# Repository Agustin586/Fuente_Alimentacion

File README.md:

# Fuente_Alimentacion
 Programa de esp32 y kicad.

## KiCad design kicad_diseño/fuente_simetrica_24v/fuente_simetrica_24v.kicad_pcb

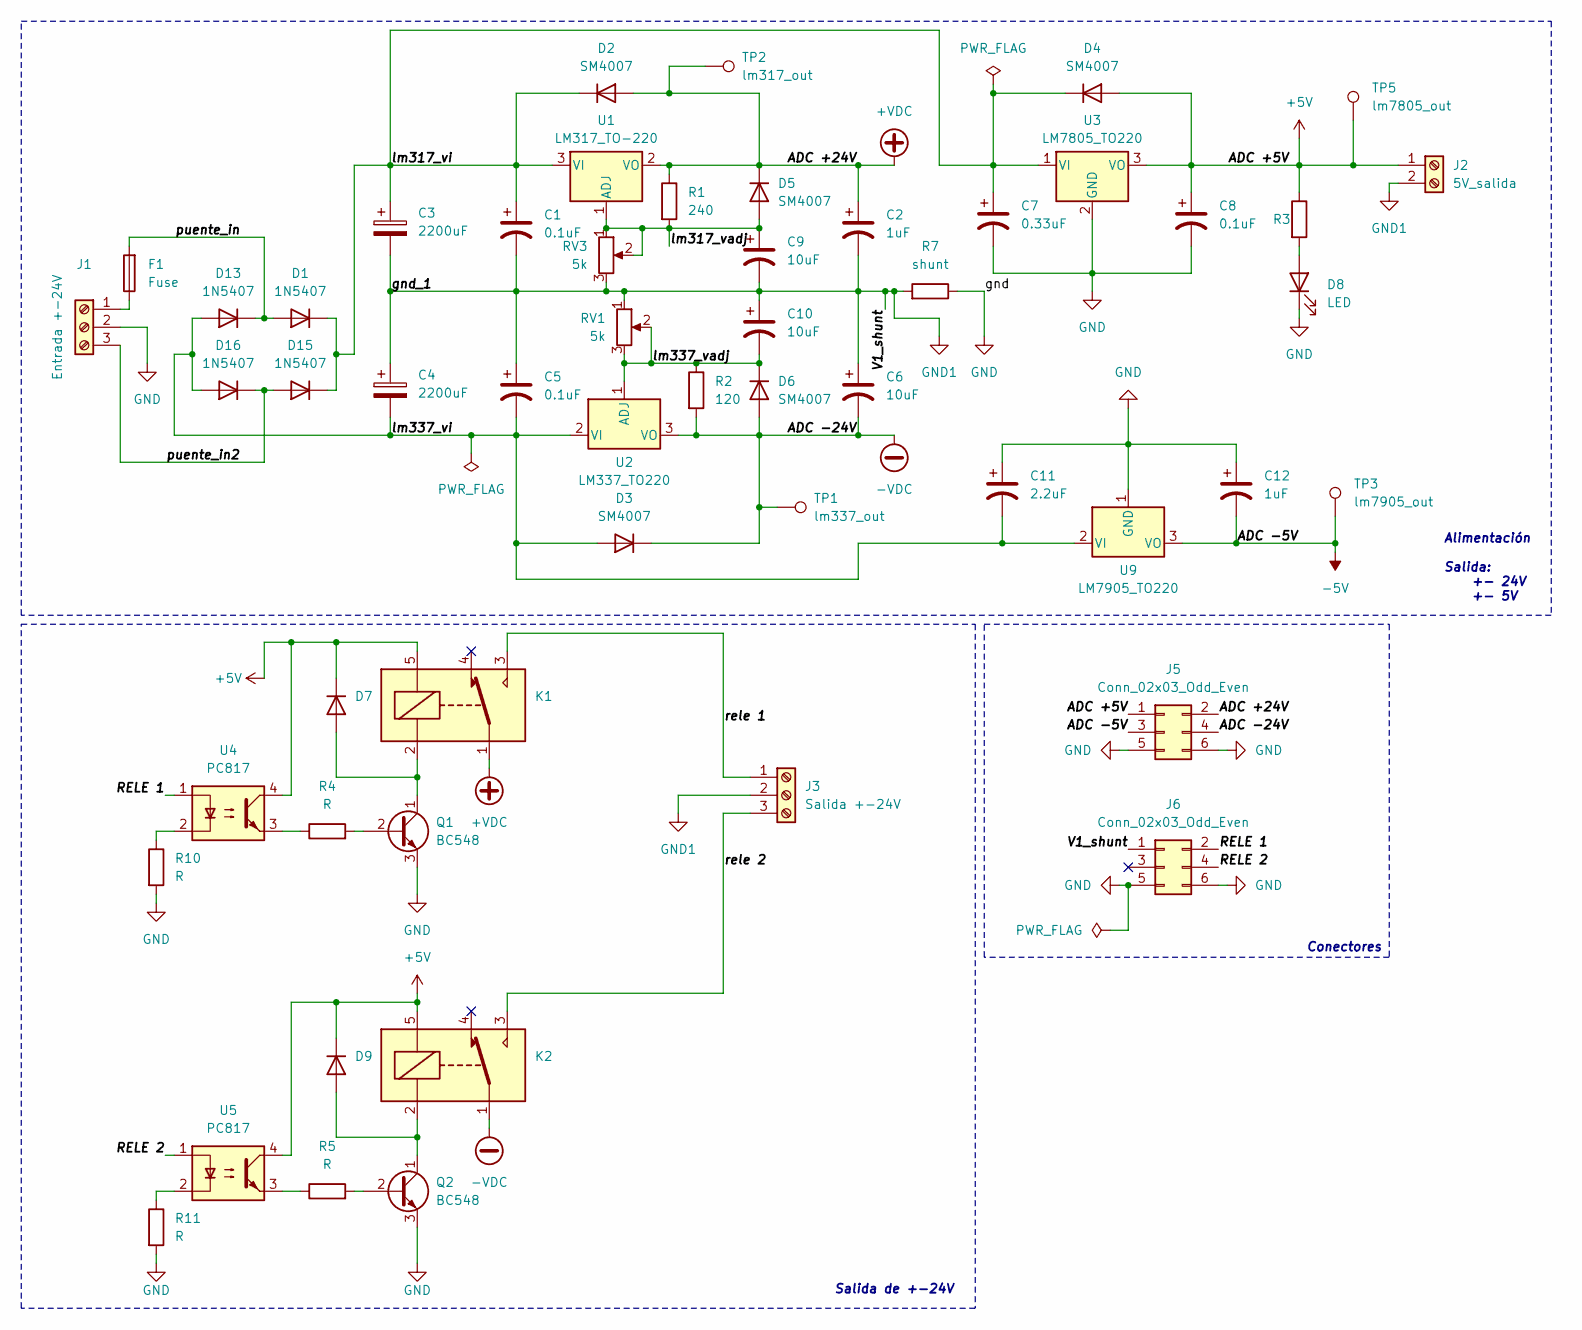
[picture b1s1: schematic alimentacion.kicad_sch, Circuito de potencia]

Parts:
C1, C5, C8: 0.1uF; CP_Radial_D5.0mm_P2.50mm
C2, C12: 1uF; CP_Radial_D5.0mm_P2.50mm
C3, C4: 2200uF; CP_Radial_D14.0mm_P5.00mm
C6, C9, C10: 10uF; CP_Radial_D5.0mm_P2.50mm
C7: 0.33uF; CP_Radial_D5.0mm_P2.50mm
C11: 2.2uF; CP_Radial_D5.0mm_P2.50mm
D1, D13, D15, D16: 1N5407; D_DO-201AD_P15.24mm_Horizontal
D2, D3, D4, D5, D6: SM4007; D_MELF
D7, D9: 1N4007; D_DO-41_SOD81_P10.16mm_Horizontal
D8: LED; LED_D5.0mm
F1: Fuse; Fuseholder_Clip-5x20mm_Littelfuse_100_Inline_P20.50x4.60mm_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
J1: Entrada +-24V; TerminalBlock_bornier-3_P5.08mm
J2: 5V_salida; TerminalBlock_bornier-2_P5.08mm
J3: Salida +-24V; TerminalBlock_bornier-3_P5.08mm
J5, J6: Conn_02x03_Odd_Even; PinHeader_2x03_P2.54mm_Horizontal
K1, K2: SANYOU_SRD_Form_C; Relay_SPDT_SANYOU_SRD_Series_Form_C
Q1, Q2: BC548; TO-92_Inline_Wide
R1: 240; R_Axial_DIN0207_L6.3mm_D2.5mm_P10.16mm_Horizontal
R2, R3: 120; R_Axial_DIN0207_L6.3mm_D2.5mm_P10.16mm_Horizontal
R4, R5, R10, R11: R; R_Axial_DIN0207_L6.3mm_D2.5mm_P10.16mm_Horizontal
R7: shunt; R_Axial_DIN0207_L6.3mm_D2.5mm_P10.16mm_Horizontal
RV1, RV3: 5k; PinHeader_1x03_P2.54mm_Vertical
TP1: lm337_out; TestPoint_Pad_D3.0mm
TP2: lm317_out; TestPoint_Pad_D3.0mm
TP3: lm7905_out; TestPoint_Pad_D3.0mm
TP5: lm7805_out; TestPoint_Pad_D3.0mm
U1: LM317_TO-220; TO-220-3_Vertical
U2: LM337_TO220; TO-220-3_Vertical
U3: LM7805_TO220; TO-220-3_Vertical
U4, U5: PC817; DIP-4_W7.62mm
U9: LM7905_TO220; TO-220-3_Vertical

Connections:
+5V: C8.1, D4.2 (A), D7.1 (K), D9.1 (K), J2.1, J5.1, K1.5, K2.5, R3.1, TP5.1, U3.3 (VO), U4.4, U5.4; also elsewhere on the board
+VDC: C2.1, D2.2 (A), D5.1 (K), J5.2, K1.1, R1.1, TP2.1, U1.2 (VO)
-5V: C12.2, J5.3, TP3.1, U9.3 (VO); also elsewhere on the board
-VDC: C6.2, D3.1 (K), D6.2 (A), J5.4, K2.1, R2.2, TP1.1, U2.3 (VO)
/alimentacion/RELE 1: J6.2, U4.1
/alimentacion/RELE 2: J6.4, U5.1
/alimentacion/lm317_vadj: C9.1, D5.2 (A), R1.2, RV3.1, RV3.2, U1.1 (ADJ)
/alimentacion/lm317_vi: C1.1, C3.1, C7.1, D1.1 (K), D2.1 (K), D4.1 (K), D15.1 (K), U1.3 (VI), U3.1 (VI)
/alimentacion/lm337_vadj: C10.2, D6.1 (K), R2.1, RV1.2, RV1.3, U2.1 (ADJ)
/alimentacion/lm337_vi: C4.2, C5.2, C11.2, D3.2 (A), D13.2 (A), D16.2 (A), U2.2 (VI), U9.2 (VI)
/alimentacion/puente_in: D1.2 (A), D13.1 (K), F1.2
/alimentacion/puente_in2: D15.2 (A), D16.1 (K), J1.3
/alimentacion/rele 1: J3.1, K1.3
/alimentacion/rele 2: J3.3, K2.3
GND: C7.2, C8.2, C11.1, C12.1, D8.1 (K), J1.2, J5.5, J5.6, J6.5, J6.6, Q1.3 (E), Q2.3 (E), R7.1, R10.2, R11.2, U3.2 (GND), U9.1 (GND)
GND1: C1.2, C2.2, C3.2, C4.1, C5.1, C6.1, C9.2, C10.1, J2.2, J3.2, J6.1, R7.2, RV1.1, RV3.3
unnamed: D7.2 (A), K1.2, Q1.1 (C)
unnamed: D8.2 (A), R3.2
unnamed: D9.2 (A), K2.2, Q2.1 (C)
unnamed: F1.1, J1.1
unnamed: Q1.2 (B), R4.2
unnamed: Q2.2 (B), R5.2
unnamed: R4.1, U4.3
unnamed: R5.1, U5.3
unnamed: R10.1, U4.2
unnamed: R11.1, U5.2

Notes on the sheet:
Alimentación Salida: +- 24V +- 5V
Conectores
Salida de +-24V

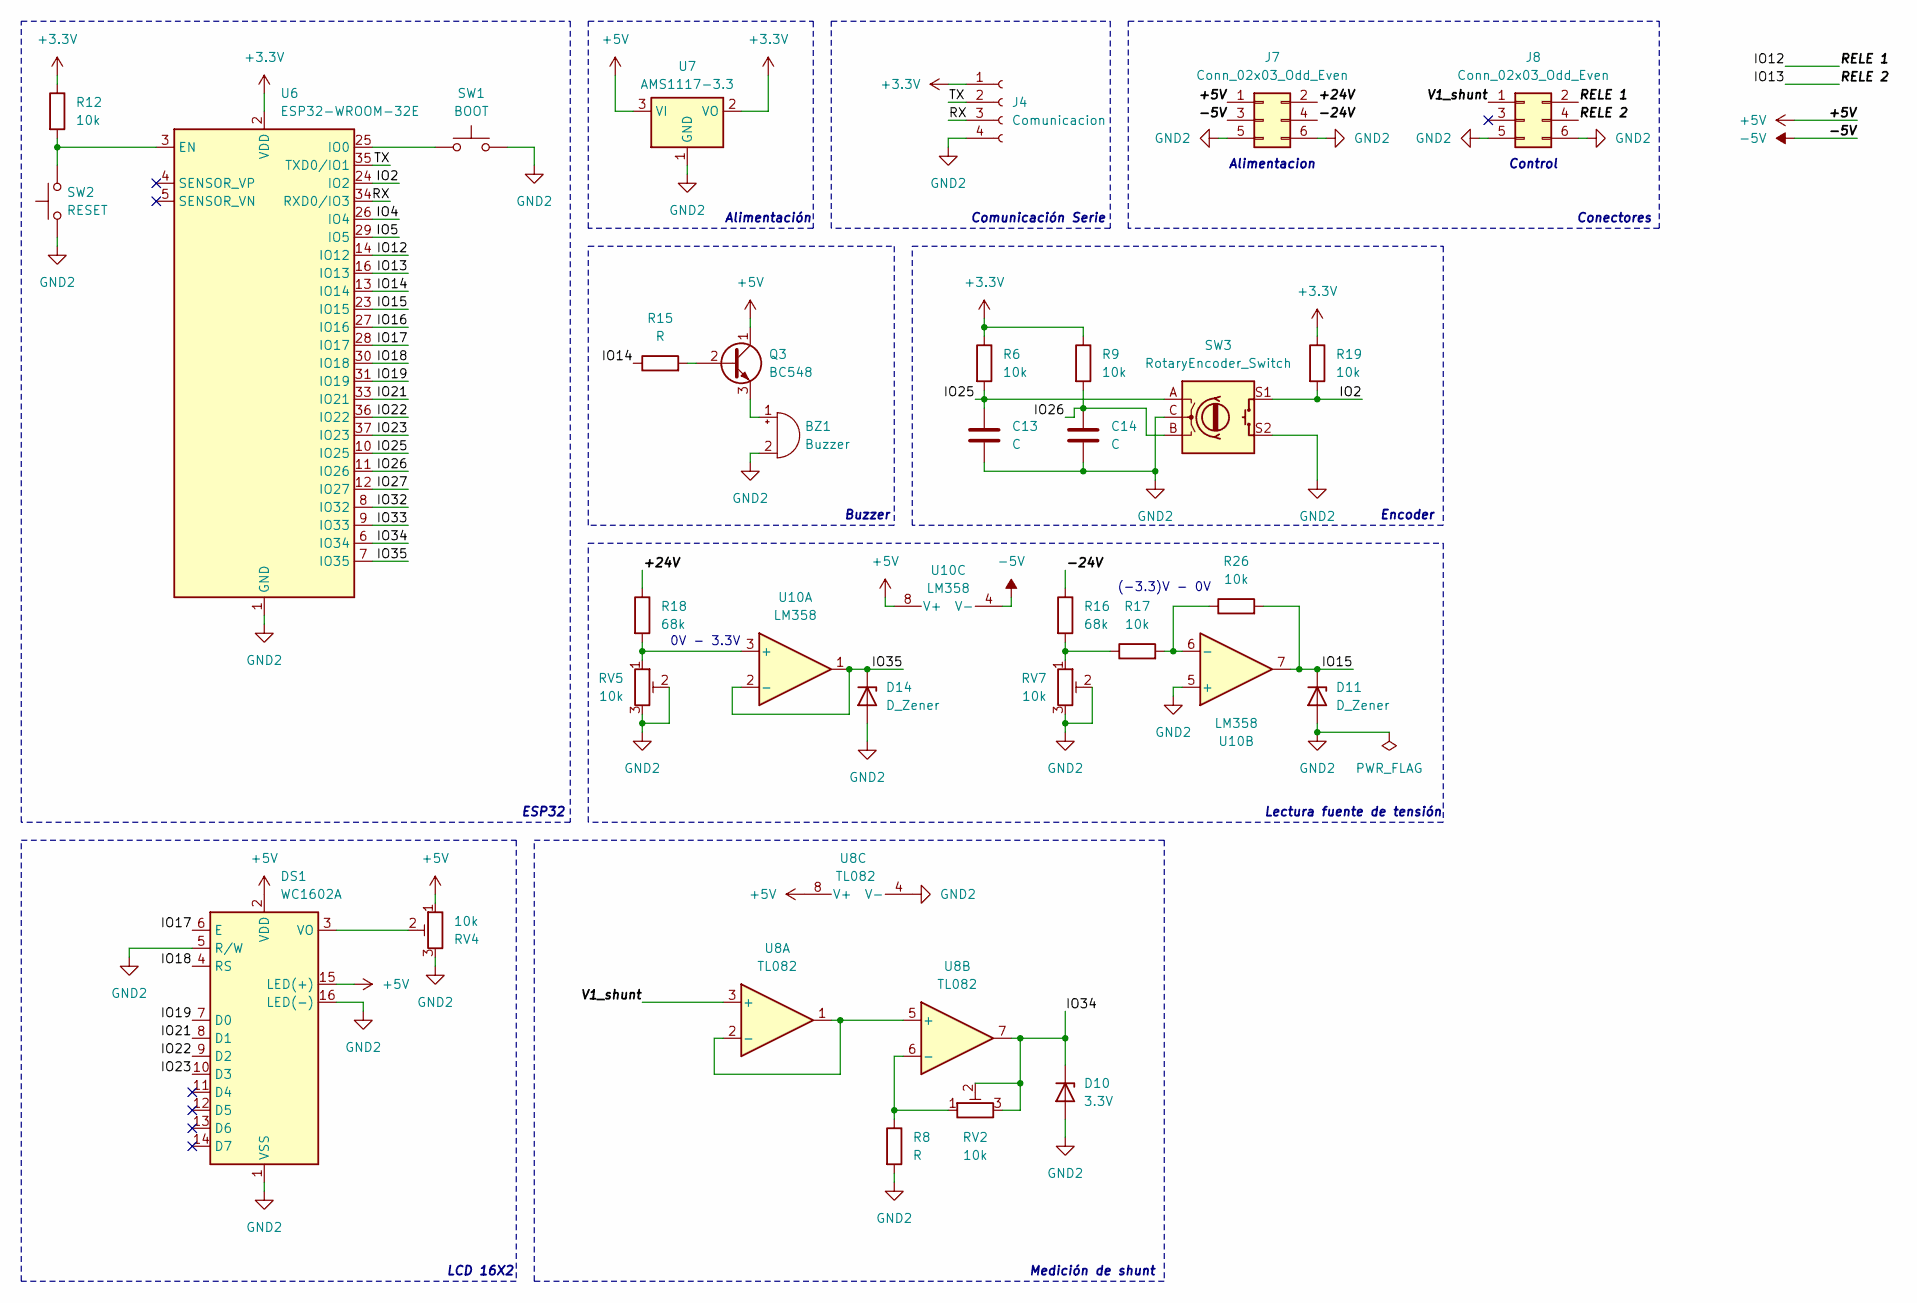
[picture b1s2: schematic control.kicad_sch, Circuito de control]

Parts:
BZ1: Buzzer; MagneticBuzzer_ProSignal_ABI-009-RC
C13, C14: C; C_Disc_D5.0mm_W2.5mm_P2.50mm
D10: 3.3V; D_DO-35_SOD27_P7.62mm_Horizontal
D11, D14: D_Zener; D_DO-35_SOD27_P7.62mm_Horizontal
DS1: WC1602A
J4: Comunicacion; PinSocket_1x04_P2.54mm_Vertical
J7, J8: Conn_02x03_Odd_Even; PinSocket_2x03_P2.54mm_Horizontal
Q3: BC548; TO-92_Inline_Wide
R6, R9, R12, R17, R19, R26: 10k; R_Axial_DIN0207_L6.3mm_D2.5mm_P10.16mm_Horizontal
R8, R15: R; R_Axial_DIN0207_L6.3mm_D2.5mm_P10.16mm_Horizontal
R16, R18: 68k; R_Axial_DIN0207_L6.3mm_D2.5mm_P10.16mm_Horizontal
RV2, RV4, RV5, RV7: 10k; Potentiometer_Bourns_3296W_Vertical
SW1: BOOT; SW_PUSH_6mm
SW2: RESET; SW_PUSH_6mm
SW3: RotaryEncoder_Switch; RotaryEncoder_Alps_EC11E-Switch_Vertical_H20mm
U6: ESP32-WROOM-32E; ESP32-WROOM-32D
U7: AMS1117-3.3; SOT-223-3_TabPin2
U8: TL082; DIP-8_W7.62mm_LongPads
U10: LM358; DIP-8_W7.62mm_LongPads

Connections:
+3.3V: J4.1, R6.1, R9.1, R12.1, R19.1, U6.2 (VDD), U7.2 (VO)
+5V: DS1.2 (VDD), DS1.15 (LED(+)), J7.1, Q3.1 (C), RV4.1, U7.3 (VI), U8.8 (V+), U10.8 (V+); also elsewhere on the board
-5V: J7.3, U10.4 (V-); also elsewhere on the board
/control/+24V: J7.2, R18.1
/control/-24V: J7.4, R16.1
/control/IO2: R19.2, SW3.S1, U6.24 (IO2)
/control/IO4: U6.26 (IO4)
/control/IO5: U6.29 (IO5)
/control/IO12: J8.2, U6.14 (IO12)
/control/IO13: J8.4, U6.16 (IO13)
/control/IO14: R15.1, U6.13 (IO14)
/control/IO15: D11.1 (K), R26.2, U6.23 (IO15), U10.7
/control/IO16: U6.27 (IO16)
/control/IO17: DS1.6 (E), U6.28 (IO17)
/control/IO18: DS1.4 (RS), U6.30 (IO18)
/control/IO19: DS1.7 (D0), U6.31 (IO19)
/control/IO21: DS1.8 (D1), U6.33 (IO21)
/control/IO22: DS1.9 (D2), U6.36 (IO22)
/control/IO23: DS1.10 (D3), U6.37 (IO23)
/control/IO25: C13.1, R6.2, SW3.A, U6.10 (IO25)
/control/IO26: C14.1, R9.2, SW3.B, U6.11 (IO26)
/control/IO27: U6.12 (IO27)
/control/IO32: U6.8 (IO32)
/control/IO33: U6.9 (IO33)
/control/IO34: D10.1 (K), RV2.2, RV2.3, U6.6 (IO34), U8.7; also elsewhere on the board
/control/IO35: D14.1 (K), U6.7 (IO35), U10.1, U10.2 (-)
/control/RX: J4.3, U6.34 (RXD0/IO3)
/control/TX: J4.2, U6.35 (TXD0/IO1)
/control/V1_shunt: J8.1, U8.3 (+); also elsewhere on the board
GND2: BZ1.2 (-), C13.2, C14.2, D10.2 (A), D11.2 (A), D14.2 (A), DS1.1 (VSS), DS1.5 (R/W), DS1.16 (LED(-)), J4.4, J7.5, J7.6, J8.5, J8.6, R8.2, RV4.3, RV5.2, RV5.3, RV7.2, RV7.3, SW1.2, SW2.1, SW3.C, SW3.S2, U6.1 (GND), U6.15 (GND), U6.38 (GND), U6.39 (GND), U7.1 (GND), U8.4 (V-), U10.5 (+)
unnamed: BZ1.1 (+), Q3.3 (E)
unnamed: DS1.3 (VO), RV4.2
unnamed: Q3.2 (B), R15.2
unnamed: R16.2, R17.1, RV7.1
unnamed: R12.2, SW2.2, U6.3 (EN)
unnamed: SW1.1, U6.25 (IO0)
unnamed: U8.1, U8.2 (-), U8.5 (+)
unnamed: R8.1, RV2.1, U8.6 (-)
unnamed: R18.2, RV5.1, U10.3 (+)
unnamed: R17.2, R26.1, U10.6 (-)

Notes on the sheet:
Encoder
Alimentación
(-3.3)V - 0V
0V - 3.3V
LCD 16X2
Medición de shunt
Lectura fuente de tensión
Control
Alimentacion
Buzzer
ESP32
Conectores
Comunicación Serie

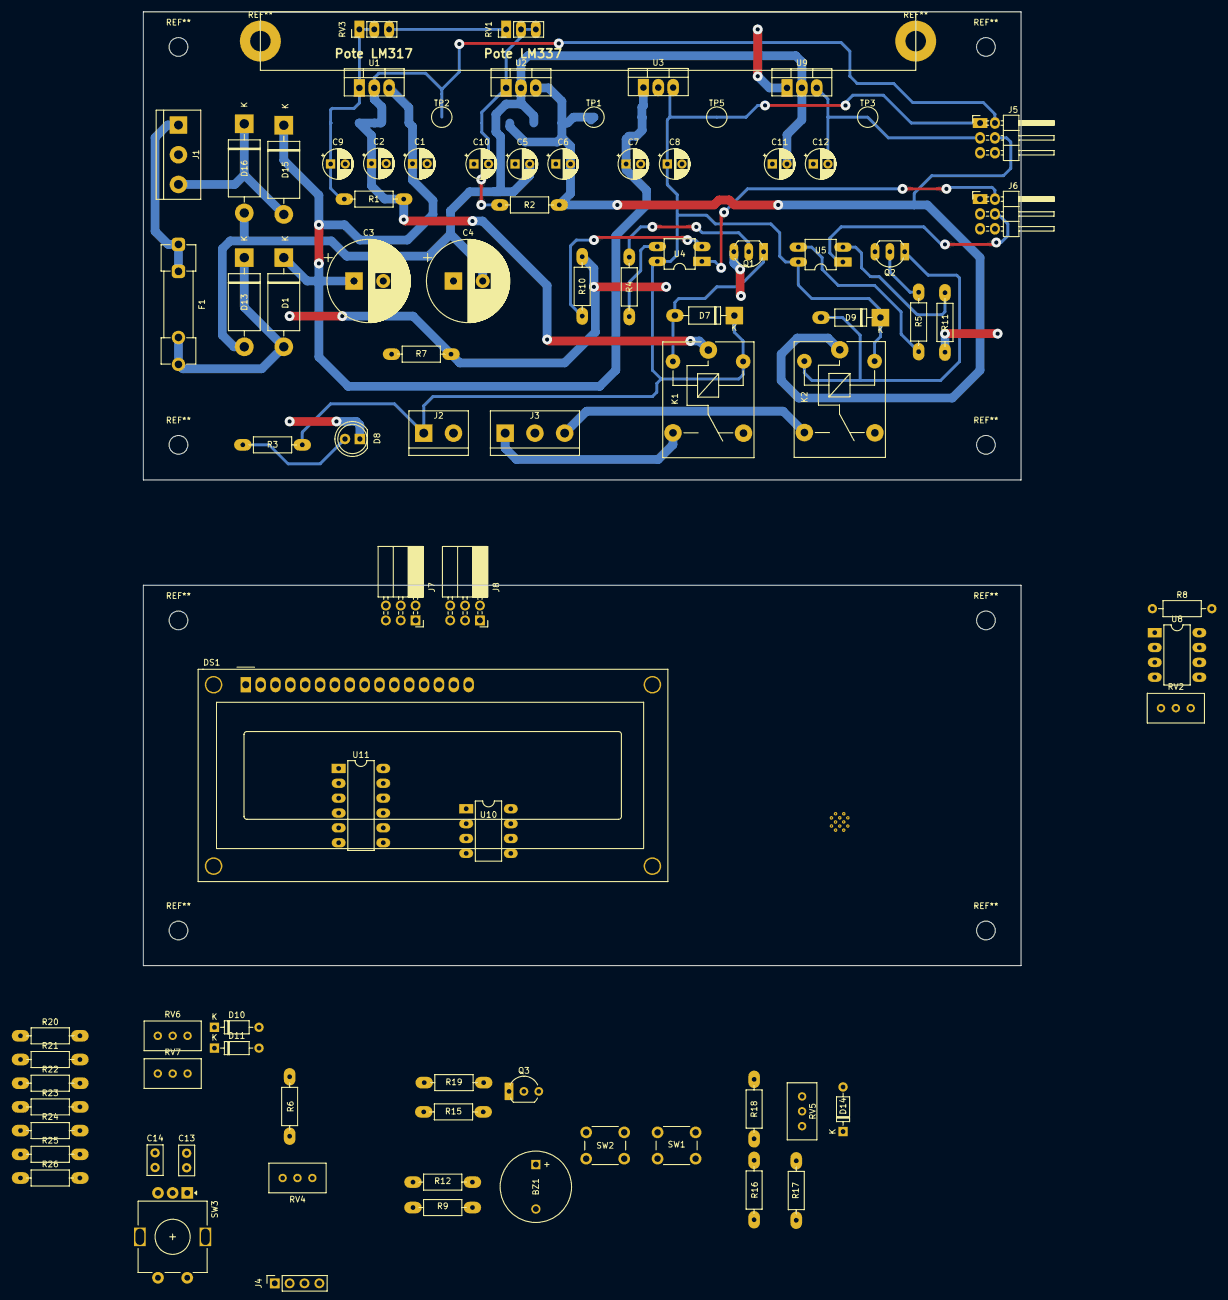
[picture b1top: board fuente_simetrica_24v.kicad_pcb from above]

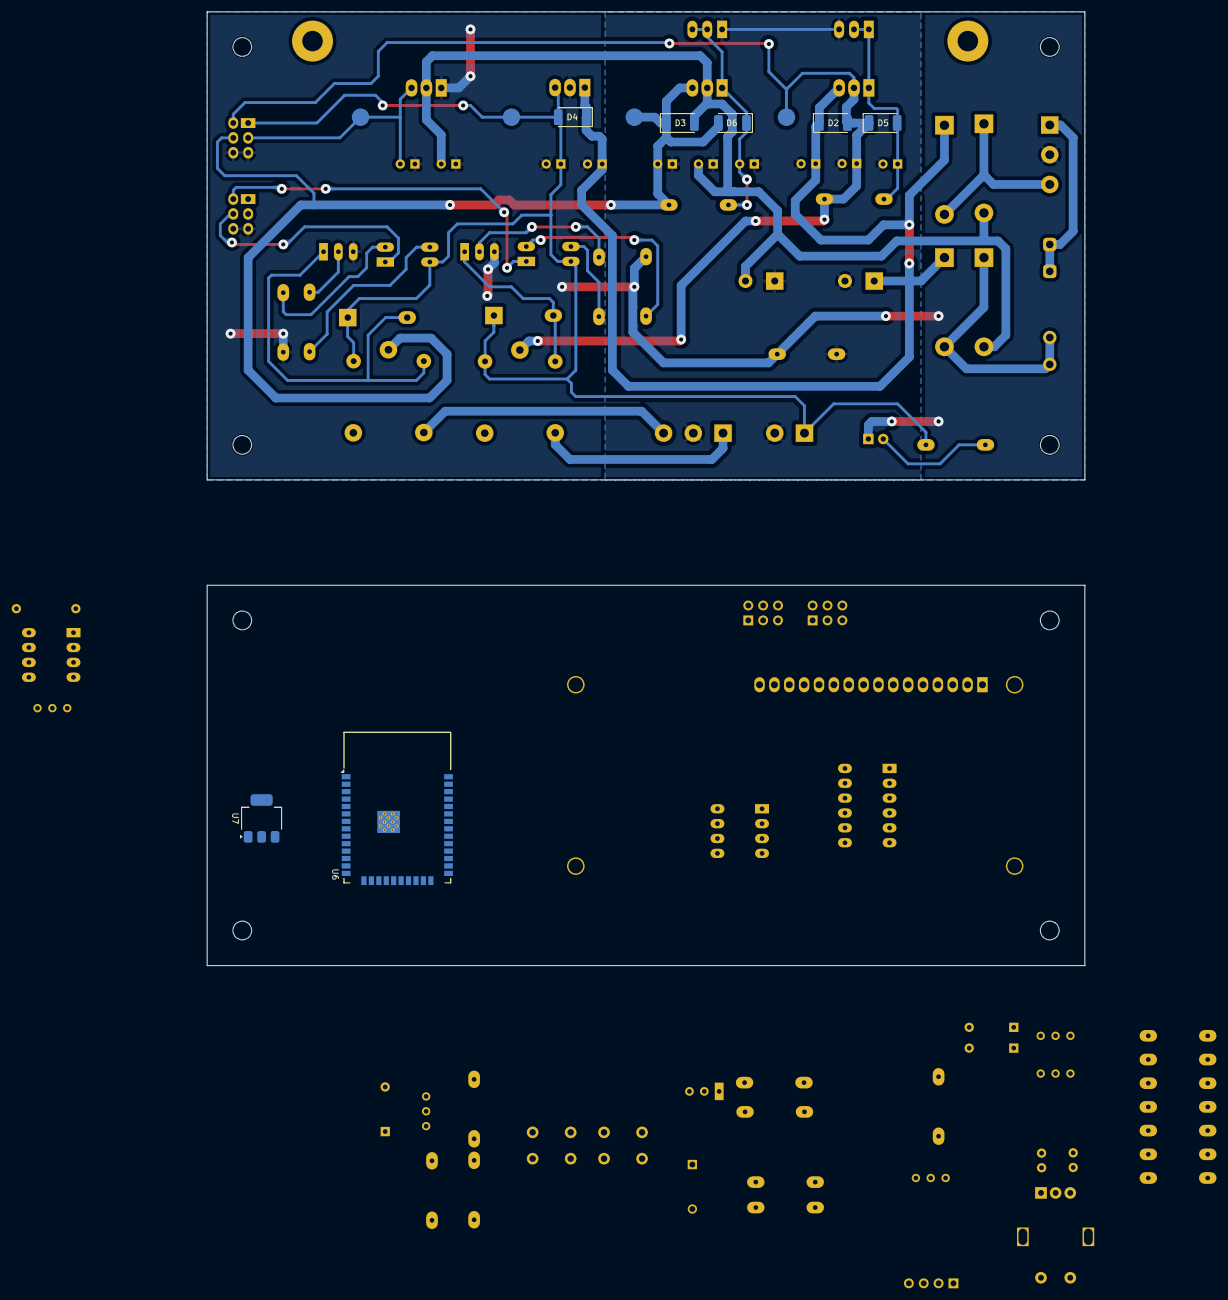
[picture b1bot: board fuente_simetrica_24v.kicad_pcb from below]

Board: 2 copper layers, 150.0 x 163.0 mm, 94 parts (7 on the bottom side), 64 nets.

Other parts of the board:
R20, R21: 50k; R_Axial_DIN0207_L6.3mm_D2.5mm_P10.16mm_Horizontal
R22, R23, R24, R25: 25k; R_Axial_DIN0207_L6.3mm_D2.5mm_P10.16mm_Horizontal
RV6: RG; Potentiometer_Bourns_3296W_Vertical
U11: LM324; DIP-12_W7.62mm_LongPads

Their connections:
+5V: U11.4 (V+); also elsewhere on the board
-5V: U11.11 (V-); also elsewhere on the board
/control/IO34: R23.2, R24.2, U11.8; also elsewhere on the board
/control/V1_shunt: U11.5 (+); also elsewhere on the board
unnamed: R20.1, R22.1, U11.1
unnamed: R21.2, R25.2, U11.7
unnamed: R20.2, RV6.1, U11.2 (-)
unnamed: R21.1, RV6.2, RV6.3, U11.6 (-)
unnamed: R24.1, R25.1, U11.10 (+)
unnamed: R22.2, R23.1, U11.9 (-)

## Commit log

2024-07-13 Update Fte - Potencia.
2024-07-13 Update Fte - Control.
2024-07-14 Update Fte - Pcb
2024-07-25 Update Fte
2024-07-27 Update Fte - Diseño de Pcb
2024-07-30 Update Fte - Fte Potencia
2024-07-30 Update Fte - Control
2024-07-31 Update Fte - Diseño ao
2024-08-02 Update Fte - Diseño pcb
